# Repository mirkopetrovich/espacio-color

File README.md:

# espacio-color

TODO :

-probar sketch en ESP32
-control leds sala

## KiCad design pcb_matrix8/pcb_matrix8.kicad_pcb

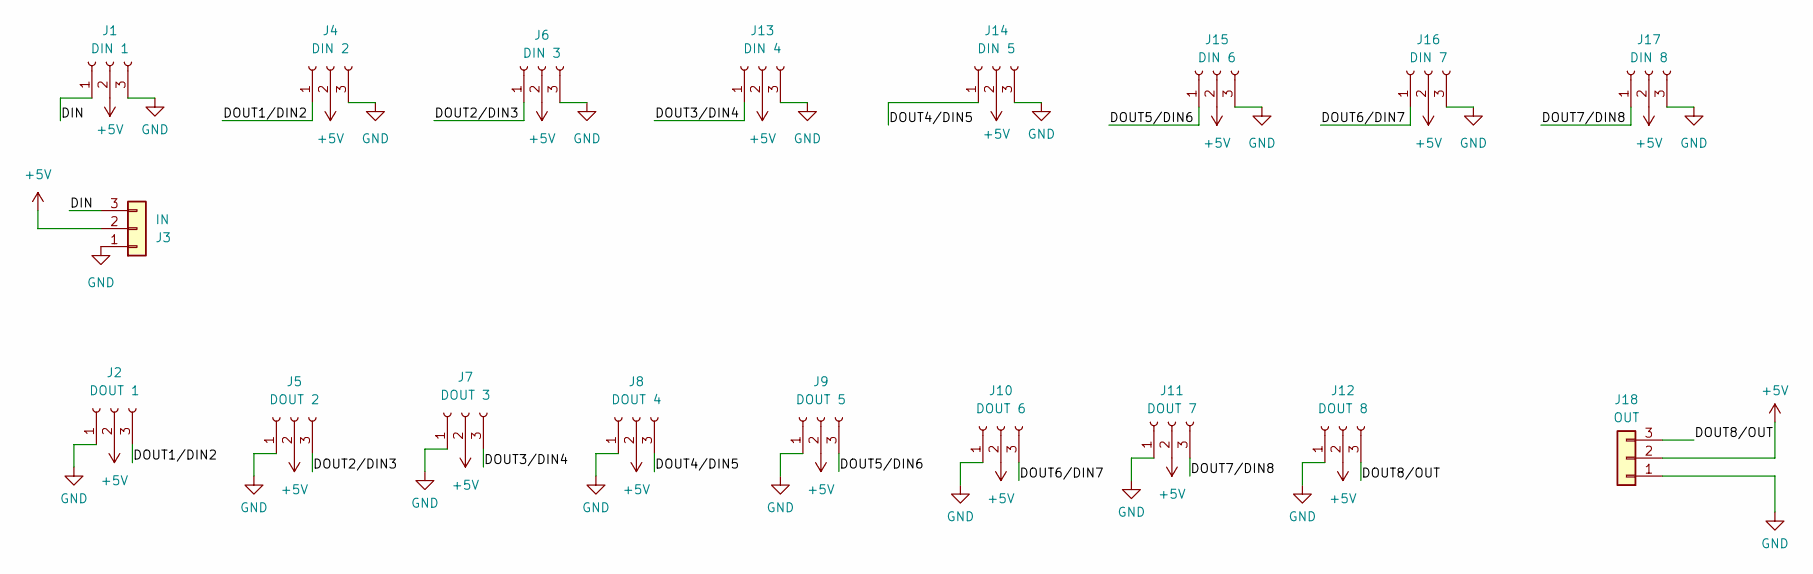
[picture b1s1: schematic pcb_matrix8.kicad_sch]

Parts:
J1: DIN 1; PinSocket_1x03_P2.54mm_Vertical
J2: DOUT 1; PinSocket_1x03_P2.54mm_Vertical
J3: IN; PinHeader_1x03_P2.54mm_Horizontal
J4: DIN 2; PinSocket_1x03_P2.54mm_Vertical
J5: DOUT 2; PinSocket_1x03_P2.54mm_Vertical
J6: DIN 3; PinSocket_1x03_P2.54mm_Vertical
J7: DOUT 3; PinSocket_1x03_P2.54mm_Vertical
J8: DOUT 4; PinSocket_1x03_P2.54mm_Vertical
J9: DOUT 5; PinSocket_1x03_P2.54mm_Vertical
J10: DOUT 6; PinSocket_1x03_P2.54mm_Vertical
J11: DOUT 7; PinSocket_1x03_P2.54mm_Vertical
J12: DOUT 8; PinSocket_1x03_P2.54mm_Vertical
J13: DIN 4; PinSocket_1x03_P2.54mm_Vertical
J14: DIN 5; PinSocket_1x03_P2.54mm_Vertical
J15: DIN 6; PinSocket_1x03_P2.54mm_Vertical
J16: DIN 7; PinSocket_1x03_P2.54mm_Vertical
J17: DIN 8; PinSocket_1x03_P2.54mm_Vertical
J18: OUT; PinHeader_1x03_P2.54mm_Horizontal

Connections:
+5V: J1.2, J2.2, J3.2, J4.2, J5.2, J6.2, J7.2, J8.2, J9.2, J10.2, J11.2, J12.2, J13.2, J14.2, J15.2, J16.2, J17.2, J18.2
/DIN: J1.1, J3.3
/DOUT1/DIN2: J2.3, J4.1
/DOUT2/DIN3: J5.3, J6.1
/DOUT3/DIN4: J7.3, J13.1
/DOUT4/DIN5: J8.3, J14.1
/DOUT5/DIN6: J9.3, J15.1
/DOUT6/DIN7: J10.3, J16.1
/DOUT7/DIN8: J11.3, J17.1
/DOUT8/OUT: J12.3, J18.3
GND: J1.3, J2.1, J3.1, J4.3, J5.1, J6.3, J7.1, J8.1, J9.1, J10.1, J11.1, J12.1, J13.3, J14.3, J15.3, J16.3, J17.3, J18.1

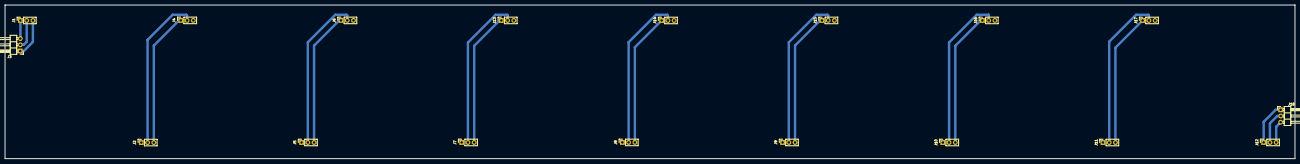
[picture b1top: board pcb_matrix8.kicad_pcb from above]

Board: 2 copper layers, 525.0 x 62.5 mm, 18 parts (0 on the bottom side), 11 nets.

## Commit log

2024-08-29 material
2024-09-02 mono
2024-09-02 fuentes matrix
2024-09-03 24x8
2024-10-14 gradiente + hex
2024-10-15 pcb 2
2024-11-07 HSL-HSV
2025-05-25 RS485
2025-06-11 patch pd
2025-06-11 sketch recibe codigos
